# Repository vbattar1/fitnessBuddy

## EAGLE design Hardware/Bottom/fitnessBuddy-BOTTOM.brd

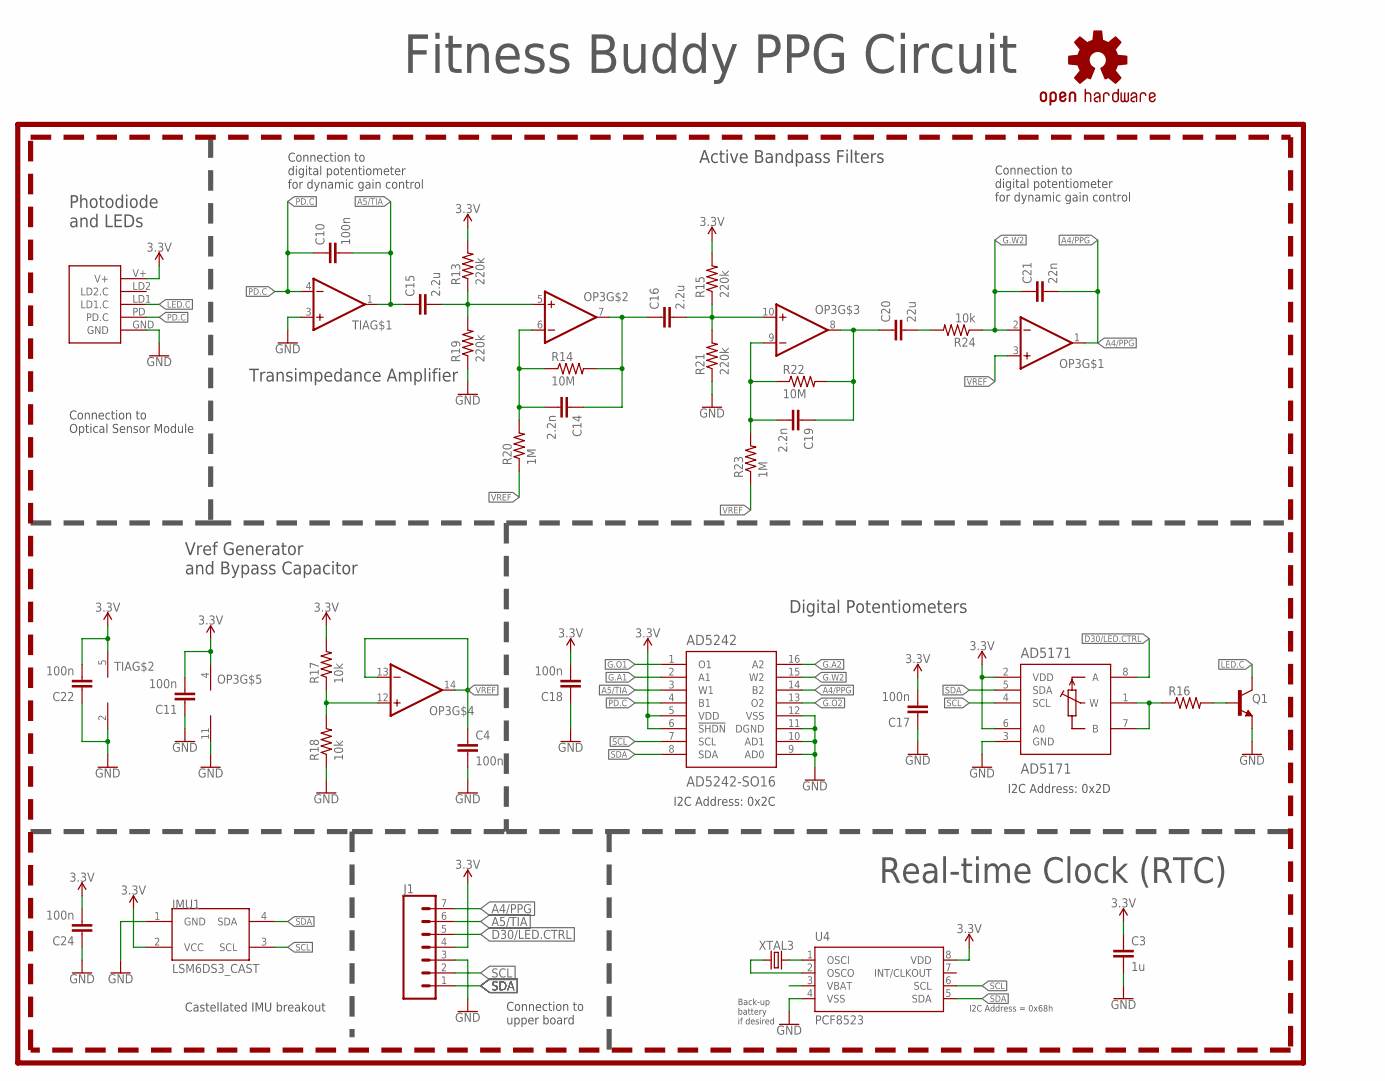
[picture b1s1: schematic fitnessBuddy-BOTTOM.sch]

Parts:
AD5171: AD5171; SOT-23-8
AD5242: AD5242-SO16; SO16
C3: 1u; C0603
C4, C10, C11, C17, C18, C22, C24: 100n; C0603
C14, C19: 2.2n; C0603
C15, C16: 2.2u; C0603
C20: 22u; C0603
C21: 22n; C0603
IMU1: LSM6DS3_CAST
J1: CONN_07-1.27MM; 1X07_1.27MM
LOGO1: REVISION.A; REV.A
LOGO2: OSHW-LOGOS; OSHW-LOGO-S
OP3: OP-QUAD-SO14; SO14
Q1: NPN-GENERIC; SOT23-3
R13, R15, R19, R21: 220k; R0603
R14, R22: 10M; R0603
R16: RESISTOR0603; R0603
R17, R18: 10k; R0402
R20, R23: 1M; R0603
R24: 10k; R0603
TIA: OP-SINGLEOT; SOT23-5
U4: PCF8523; SO8; DIGIKEY 568-5306-1-ND
U$3: PPG.MODULE.2
XTAL3: 32.7680kHz; 2-SMD.NOLEAD.2.0MMTO1.2MM

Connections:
3.3V: AD5171.2 (VDD), AD5171.6 (A0), AD5242.5 (VDD), AD5242.6 (!SHDN), C3.1, C11.2, C17.2, C18.2, C22.2, C24.2, IMU1.2 (VCC), J1.4, OP3.4 (V+), R13.2, R15.2, R17.2, TIA.5 (V+), U4.8 (VDD), U$3.V+
A4/PPG: AD5242.14 (B2), C21.2, J1.7, OP3.1 (OUT)
A5/TIA: AD5242.3 (W1), C10.2, C15.1, J1.6, TIA.1 (OUT)
D30/LED.CTRL: AD5171.8 (A), J1.5
G.A1: AD5242.2 (A1)
G.A2: AD5242.16 (A2)
G.O1: AD5242.1 (O1)
G.O2: AD5242.13 (O2)
G.W2: AD5242.15 (W2), C21.1, OP3.2 (-IN), R24.1
GND: AD5171.3 (GND), AD5242.9 (AD0), AD5242.10 (AD1), AD5242.11 (DGND), AD5242.12 (VSS), C3.2, C4.2, C11.1, C17.1, C18.1, C22.1, C24.1, IMU1.1 (GND), J1.3, OP3.11 (V-), Q1.2 (E), R18.1, R19.1, R21.1, TIA.2 (V-), TIA.3 (+IN), U4.4 (VSS), U$3.GND
LED.C: Q1.3 (C), U$3.LD1 (LD1.C)
unnamed: U4.2 (OSCO), XTAL3.P$1 (1)
unnamed: U4.1 (OSCI), XTAL3.P$2 (2)
unnamed: Q1.1 (B), R16.2
unnamed: AD5171.1 (W), AD5171.7 (B), R16.1
unnamed: OP3.12 (+IN), R17.1, R18.2
unnamed: C15.2, OP3.5 (+IN), R13.1, R19.2
unnamed: C14.2, OP3.6 (-IN), R14.1, R20.2
unnamed: C14.1, C16.1, OP3.7 (OUT), R14.2
unnamed: C16.2, OP3.10 (+IN), R15.1, R21.2
unnamed: C19.2, OP3.9 (-IN), R22.1, R23.2
unnamed: C19.1, C20.1, OP3.8 (OUT), R22.2
unnamed: C20.2, R24.2
PD.C: AD5242.4 (B1), C10.1, TIA.4 (-IN), U$3.PD (PD.C)
SCL: AD5171.4 (SCL), AD5242.7 (SCL), IMU1.3 (SCL), J1.2, U4.6 (SCL)
SDA: AD5171.5 (SDA), AD5242.8 (SDA), IMU1.4 (SDA), J1.1, U4.5 (SDA)
VBATT: U4.3 (VBAT)
VREF: C4.1, OP3.3 (+IN), OP3.13 (-IN), OP3.14 (OUT), R20.1, R23.1

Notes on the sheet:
Photodiode and LEDs
Active Bandpass Filters
Digital Potentiometers
Transimpedance Amplifier
I2C Address: 0x2C
I2C Address: 0x2D
I2C Address = 0x68h
Back-up battery if desired
Real-time Clock (RTC)
Connection to Optical Sensor Module
Connection to digital potentiometer for dynamic gain control
Connection to upper board
Castellated IMU breakout
Vref Generator and Bypass Capacitor
Fitness Buddy PPG Circuit

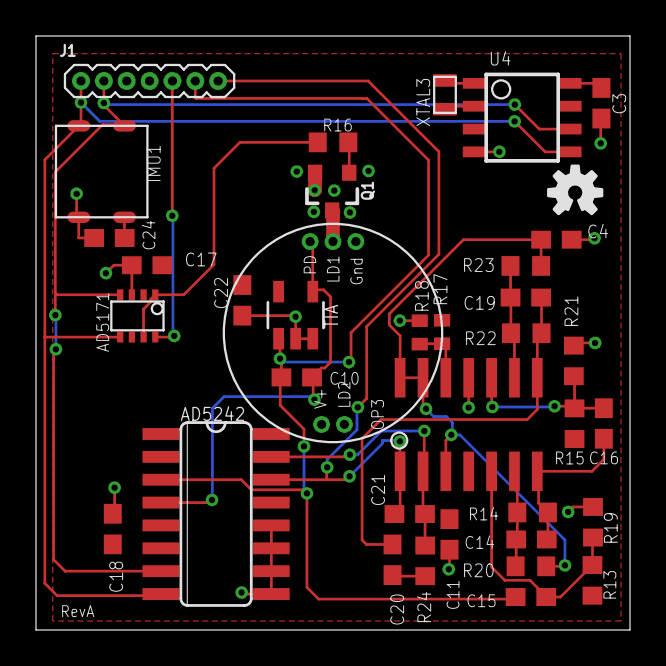
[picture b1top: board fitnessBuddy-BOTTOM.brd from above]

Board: 2 copper layers, 33.0 x 33.0 mm, 38 parts (0 on the bottom side), 23 nets.

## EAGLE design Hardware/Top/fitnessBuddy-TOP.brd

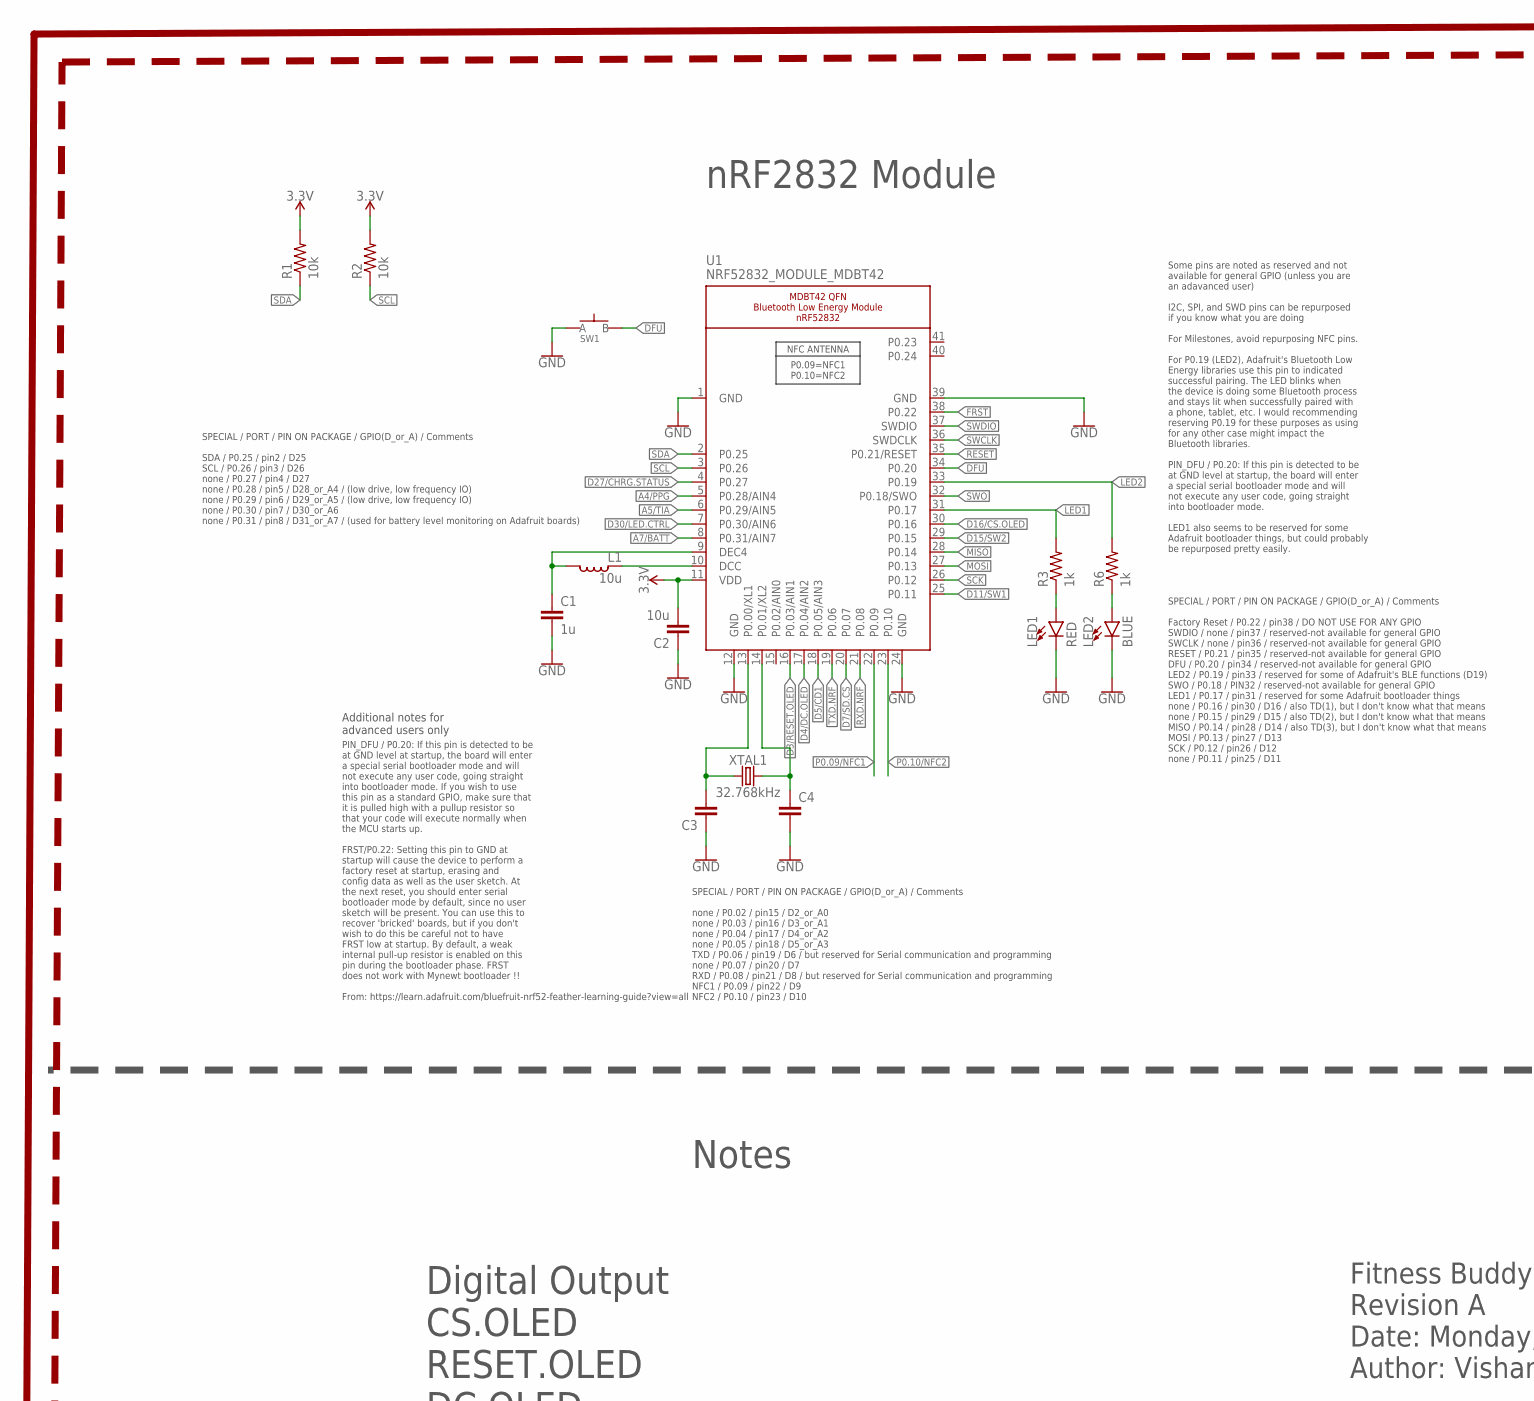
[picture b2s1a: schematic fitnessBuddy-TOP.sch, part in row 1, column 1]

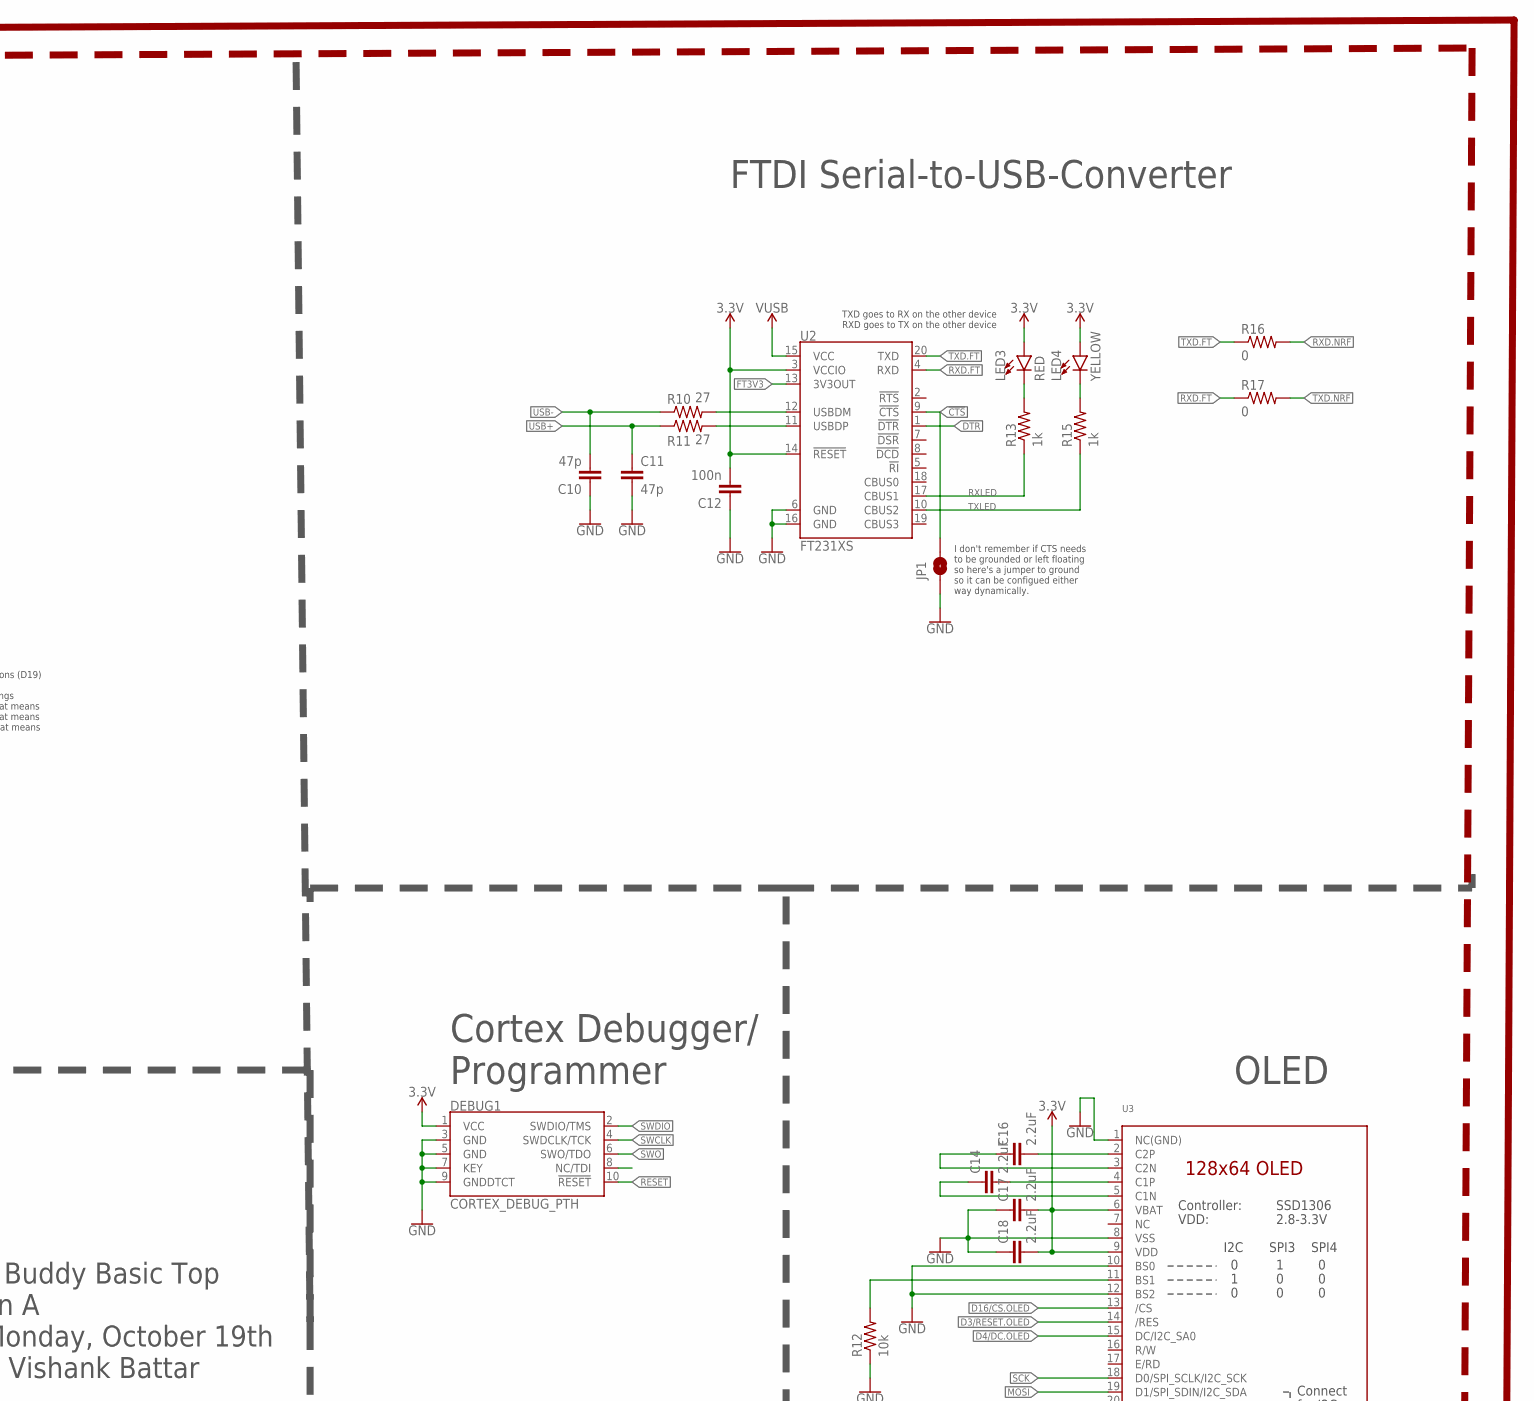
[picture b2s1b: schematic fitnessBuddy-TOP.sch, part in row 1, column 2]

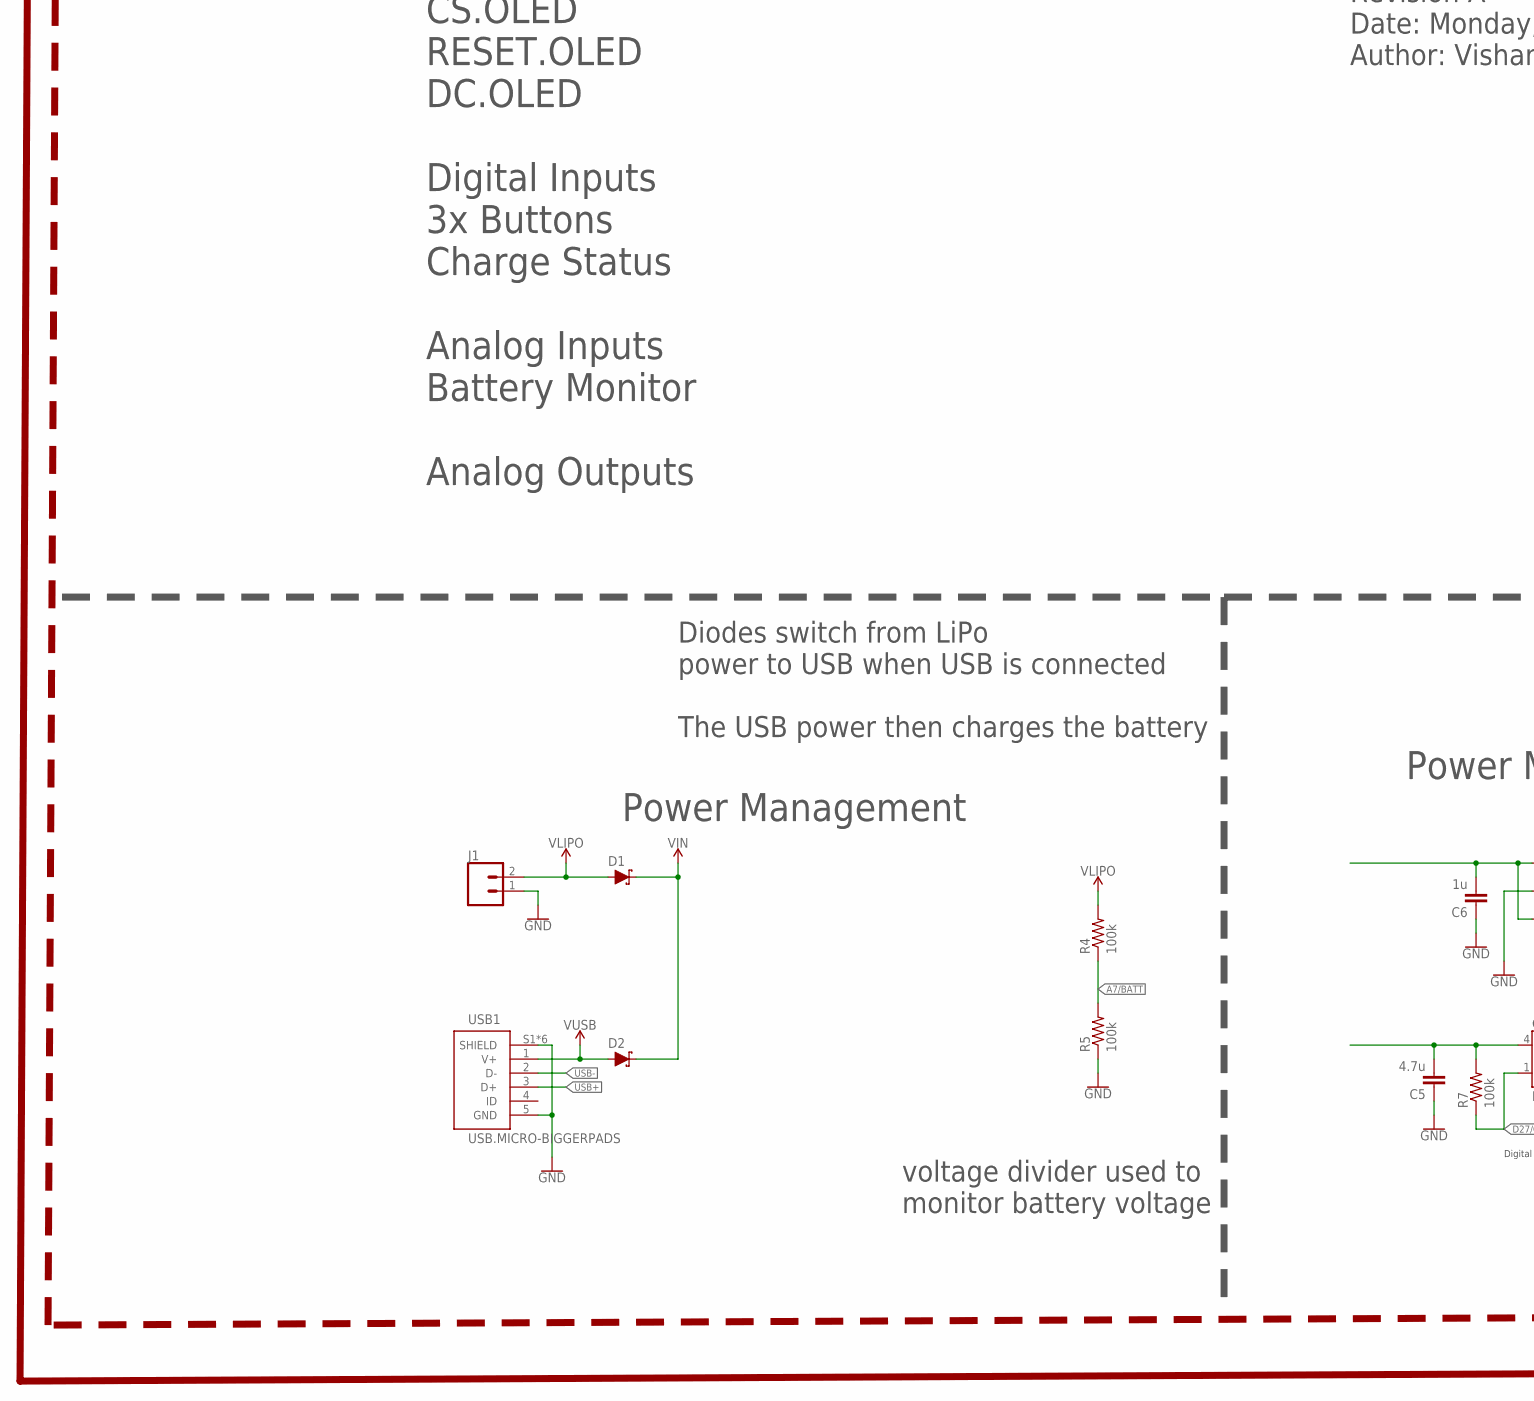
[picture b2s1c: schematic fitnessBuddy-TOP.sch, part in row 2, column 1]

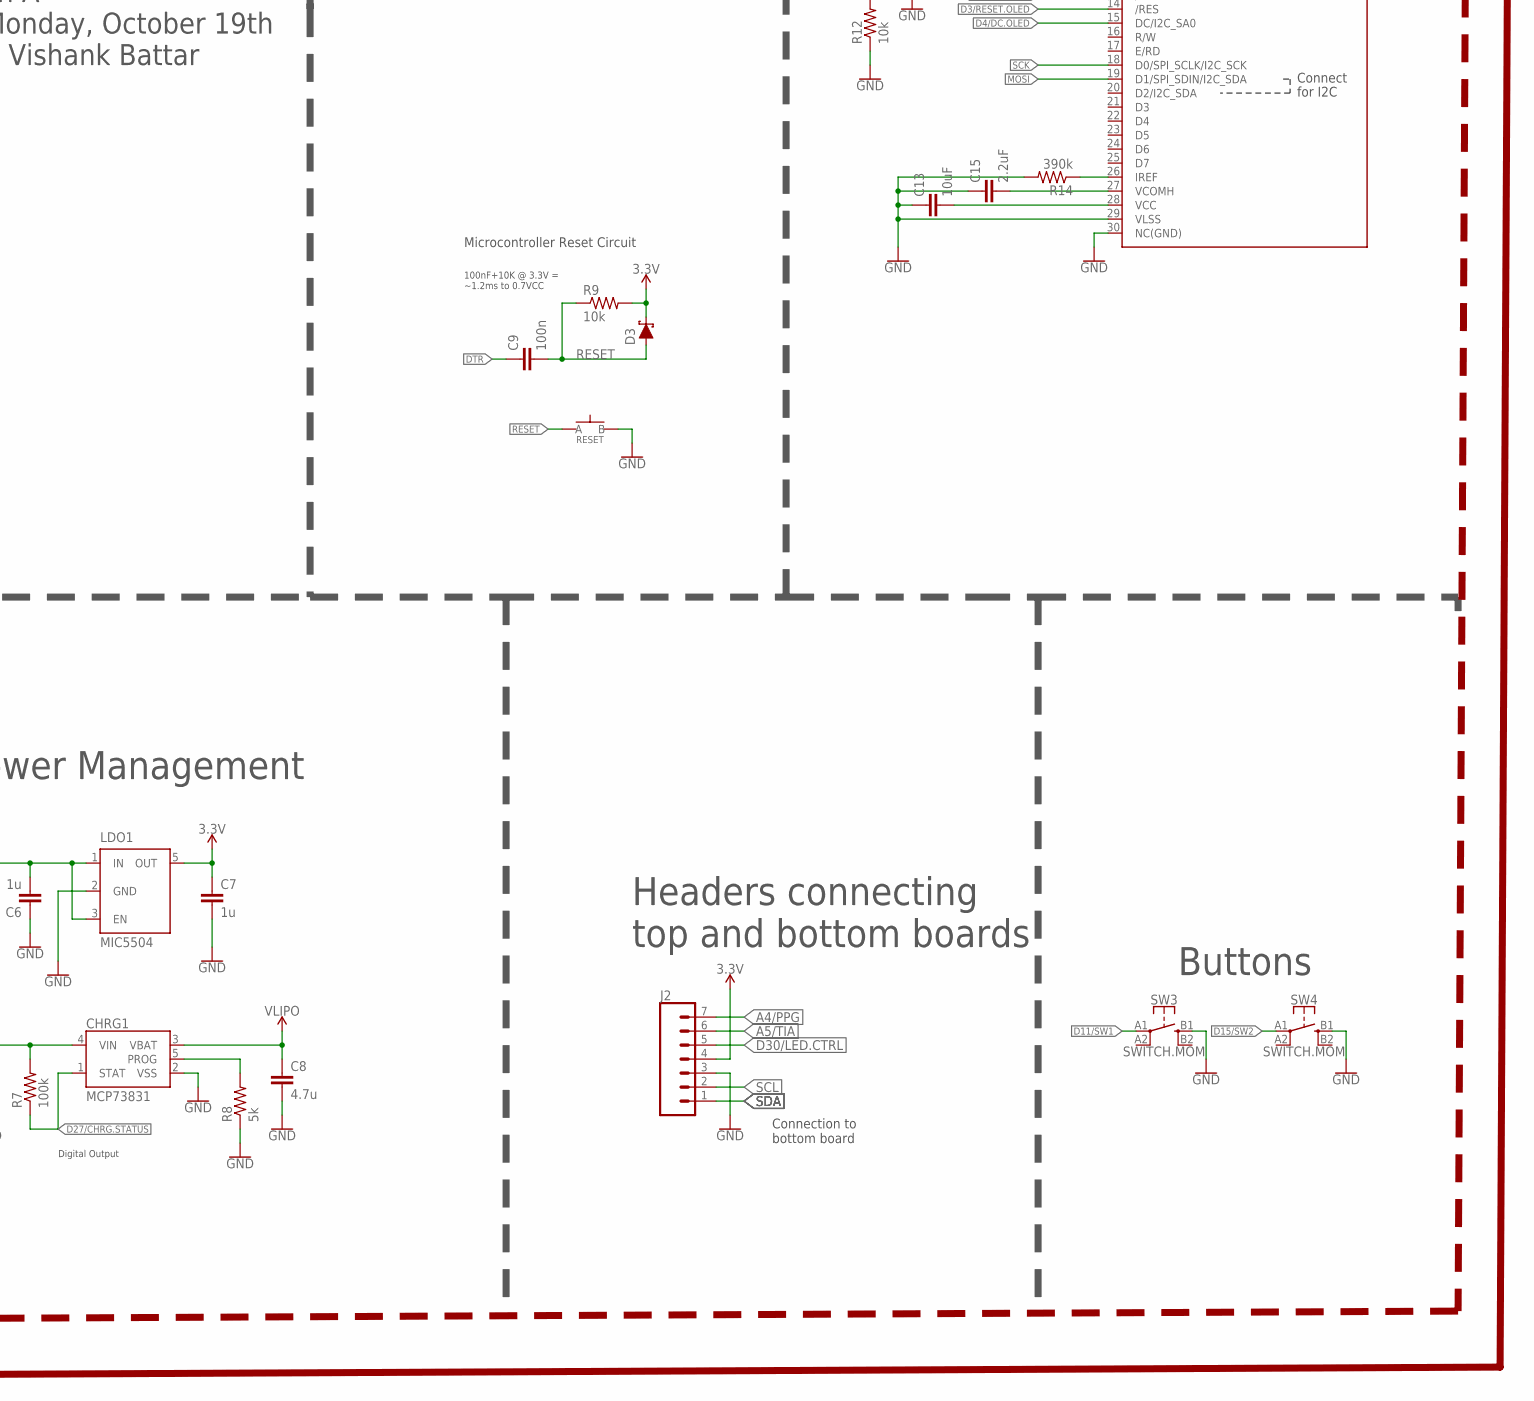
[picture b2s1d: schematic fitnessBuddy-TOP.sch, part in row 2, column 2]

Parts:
C1, C6, C7: 1u; C0603
C2: 10u; C0805
C3, C4: CAPACITOR0603; C0603
C5, C8: 4.7u; C0603
C9, C12: 100n; C0603
C10, C11: 47p; C0603
C13: 10uF; C0603
C14, C16, C17, C18: 2.2uF; C0402
C15: 2.2uF; C0603
CHRG1: MCP73831; SOT23-5
D1, D2, D3: SCHOTTKY-USC; USC
DEBUG1: CORTEX_DEBUG_PTH; 2X5-PTH-1.27MM
J1: CONN_02; 1X02
J2: CONN_07-1.27MM; 1X07_1.27MM
JP1: JUMPER-SMT_2_NO_SILK; SMT-JUMPER_2_NO_SILK
L1: 10u; L0603
LDO1: MIC5504; SOT23-5
LED1, LED3: RED; LED-0603
LED2: BLUE; LED-0603
LED4: YELLOW; LED-0603
R1, R2, R9, R12: 10k; R0603
R3, R6, R13, R15: 1k; R0603
R4, R5, R7: 100k; R0603
R8: 5k; R0603
R10, R11: 27; R0603
R14: 390k; R0603
R16, R17: 0; R0603
RESET: SPST-PTS830GG140-COPY.1-3; BUTTON-GULLWING
SW1: SPST-PTS830GG140-COPY.1-3; BUTTON-GULLWING
SW3, SW4: SWITCH.MOM; TACTILE_SWITCH_SMD_6.2MM_TALL
U1: NRF52832_MODULE_MDBT42; BLE_MODULE_RAYTAC_MDBT42
U2: FT231XS; SSOP20_L
U3: DISP_OLED_UG-2864HSWEG01-NO-WRAPAROUND; UG-2864HSWEG01_0.96IN_NO-WRAPAROUND
USB1: USB.MICRO-BIGGERPADS; USB-MICRO-01.BIGGERPADS
XTAL1: 32.768kHz; 2-SMD.NOLEAD.2.0MMTO1.2MM

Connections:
3.3V: C2.2, C7.1, C12.2, C17.2, C18.2, D3.- (C), DEBUG1.1 (VCC), J2.4, LDO1.5 (OUT), LED3.A, LED4.A, R1.2, R2.2, R9.2, U1.11 (VDD), U2.3 (VCCIO), U2.14 (!RESET), U3.6 (VBAT), U3.9 (VDD)
!CTS: JP1.2, U2.9 (!CTS)
A4/PPG: J2.7, U1.5 (P0.28/AIN4)
A5/TIA: J2.6, U1.6 (P0.29/AIN5)
A7/BATT: R4.1, R5.2, U1.8 (P0.31/AIN7)
D3/RESET.OLED: U1.16 (P0.03/AIN1), U3.14 (/RES)
D4/DC.OLED: U1.17 (P0.04/AIN2), U3.15 (DC/I2C_SA0)
D5/CD1: U1.18 (P0.05/AIN3)
D7/SD.CS: U1.20 (P0.07)
D11/SW1: SW3.A1 (1), U1.25 (P0.11)
D15/SW2: SW4.A1 (1), U1.29 (P0.15)
D16/CS.OLED: U1.30 (P0.16), U3.13 (/CS)
D27/CHRG.STATUS: CHRG1.1 (STAT), R7.1, U1.4 (P0.27)
D30/LED.CTRL: J2.5, U1.7 (P0.30/AIN6)
DFU: SW1.3 (B), U1.34 (P0.20)
DTR: C9.1, U2.1 (!DTR)
FRST: U1.38 (P0.22)
FT3V3: U2.13 (3V3OUT)
GND: C1.2, C2.1, C3.1, C4.2, C5.1, C6.1, C7.2, C8.2, C10.1, C11.2, C12.1, C13.1, C15.1, C17.1, C18.1, CHRG1.2 (VSS), DEBUG1.3 (GND), DEBUG1.5 (GND), DEBUG1.7 (KEY), DEBUG1.9 (GNDDTCT), J1.1, J2.3, JP1.1, LDO1.2 (GND), LED1.C, LED2.C, R5.1, R8.1, R12.1, R14.2, RESET.3 (B), SW1.1 (A), SW3.B1 (3), SW4.B1 (3), U1.1 (GND), U1.12 (GND), U1.24 (GND), U1.39 (GND), U2.6 (GND), U2.16 (GND), U3.1 (NC(GND)), U3.8 (VSS), U3.10 (BS0), U3.12 (BS2), U3.29 (VLSS), U3.30 (NC(GND)), USB1.5 (GND), USB1.S1 (SHIELD), USB1.S2 (SHIELD), USB1.S3 (SHIELD), USB1.S4 (SHIELD), USB1.S5 (SHIELD), USB1.S6 (SHIELD)
LED1: R3.2, U1.31 (P0.17)
LED2: R6.2, U1.33 (P0.19)
MISO: U1.28 (P0.14)
MOSI: U1.27 (P0.13), U3.19 (D1/SPI_SDIN/I2C_SDA)
unnamed: R12.2, U3.11 (BS1)
unnamed: R14.1, U3.26 (IREF)
unnamed: C16.2, U3.2 (C2P)
unnamed: C3.2, U1.13 (P0.00/XL1), XTAL1.P$1 (1)
unnamed: C16.1, U3.3 (C2N)
unnamed: C4.1, U1.14 (P0.01/XL2), XTAL1.P$2 (2)
unnamed: C14.2, U3.4 (C1P)
unnamed: C14.1, U3.5 (C1N)
unnamed: LED1.A, R3.1
unnamed: LED2.A, R6.1
unnamed: L1.1, U1.10 (DCC)
unnamed: C1.1, L1.2, U1.9 (DEC4)
unnamed: C13.2, U3.28 (VCC)
unnamed: C15.2, U3.27 (VCOMH)
unnamed: CHRG1.5 (PROG), R8.2
unnamed: C5.2, CHRG1.4 (VIN), R7.2
unnamed: R10.2, U2.12 (USBDM)
unnamed: R11.2, U2.11 (USBDP)
unnamed: LED3.C, R13.2
unnamed: LED4.C, R15.2
P0.09/NFC1: U1.22 (P0.09)
P0.10/NFC2: U1.23 (P0.10)
RESET: C9.2, D3.+ (A), DEBUG1.10 (!RESET), R9.1, RESET.1 (A), U1.35 (P0.21/RESET)
RXD.FT: R17.1, U2.4 (RXD)
RXD.NRF: R16.2, U1.21 (P0.08)
RXLED: R13.1, U2.17 (CBUS1)
SCK: U1.26 (P0.12), U3.18 (D0/SPI_SCLK/I2C_SCK)
SCL: J2.2, R2.1, U1.3 (P0.26)
SDA: J2.1, R1.1, U1.2 (P0.25)
SWCLK: DEBUG1.4 (SWDCLK/TCK), U1.36 (SWDCLK)
SWDIO: DEBUG1.2 (SWDIO/TMS), U1.37 (SWDIO)
SWO: DEBUG1.6 (SWO/TDO), U1.32 (P0.18/SWO)
TXD.FT: R16.1, U2.20 (TXD)
TXD.NRF: R17.2, U1.19 (P0.06)
TXLED: R15.1, U2.10 (CBUS2)
USB+: C11.1, R11.1, USB1.3 (D+)
USB-: C10.2, R10.1, USB1.2 (D-)
VIN: C6.2, D1.- (C), D2.- (C), LDO1.1 (IN), LDO1.3 (EN)
VLIPO: C8.1, CHRG1.3 (VBAT), D1.+ (A), J1.2, R4.2
V_USB: D2.+ (A), U2.15 (VCC), USB1.1 (V+)

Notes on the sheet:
Microcontroller Reset Circuit
100nF+10K @ 3.3V = ~1.2ms to 0.7VCC
SPECIAL / PORT / PIN ON PACKAGE / GPIO(D_or_A) / Comments SDA / P0.25 / pin2 / D25 SCL / P0.26 / pin3 / D26 none / P0.27 / pin4 / D27 none / P0.28 / pin5 / D28_or_A4 / (low drive, low frequency IO) none / P0.29 / pin6 / D29_or_A5 / (low drive, low frequency IO) none / P0.30 / pin7 / D30_or_A6 none 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
SPECIAL / PORT / PIN ON PACKAGE / GPIO(D_or_A) / Comments none / P0.02 / pin15 / D2_or_A0 none / P0.03 / pin16 / D3_or_A1 none / P0.04 / pin17 / D4_or_A2 none / P0.05 / pin18 / D5_or_A3 TXD / P0.06 / pin19 / D6 / but reserved for Serial communication and programming none / P0.07 / pin20 / D7 RXD / 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
SPECIAL / PORT / PIN ON PACKAGE / GPIO(D_or_A) / Comments Factory Reset / P0.22 / pin38 / DO NOT USE FOR ANY GPIO SWDIO / none / pin37 / reserved-not available for general GPIO SWCLK / none / pin36 / reserved-not available for general GPIO RESET / P0.21 / pin35 / reserved-not available for general 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
Some pins are noted as reserved and not available for general GPIO (unless you are an adavanced user) I2C, SPI, and SWD pins can be repurposed if you know what you are doing For Milestones, avoid repurposing NFC pins. For P0.19 (LED2), Adafruit's Bluetooth Low Energy libraries use this pin to indic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
PIN_DFU / P0.20: If this pin is detected to be at GND level at startup, the board will enter a special serial bootloader mode and will not execute any user code, going straight into bootloader mode. If you wish to use this pin as a standard GPIO, make sure that it is pulled high with a pullup resis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
Additional notes for advanced users only
nRF2832 Module
OLED
Power Management
Buttons
Cortex Debugger/ Programmer
Digital Output CS.OLED RESET.OLED DC.OLED Digital Inputs 3x Buttons Charge Status Analog Inputs Battery Monitor Analog Outputs
TXD goes to RX on the other device RXD goes to TX on the other device
I don't remember if CTS needs to be grounded or left floating so here's a jumper to ground so it can be configued either way dynamically.
FTDI Serial-to-USB-Converter
Notes
Connection to bottom board
Digital Output
Fitness Buddy Basic Top Revision A Date: Monday, October 19th Author: Vishank Battar
Diodes switch from LiPo power to USB when USB is connected The USB power then charges the battery
voltage divider used to monitor battery voltage
Headers connecting top and bottom boards

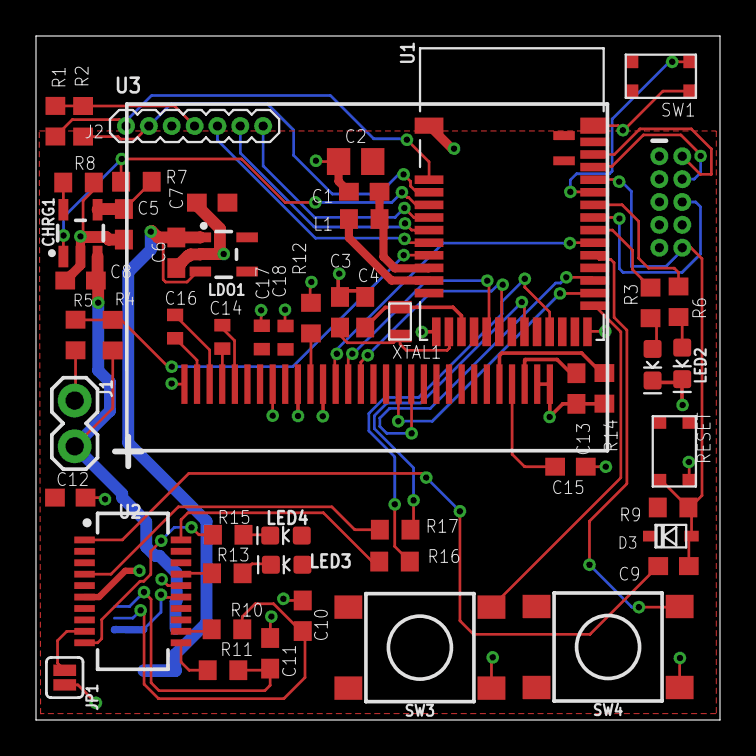
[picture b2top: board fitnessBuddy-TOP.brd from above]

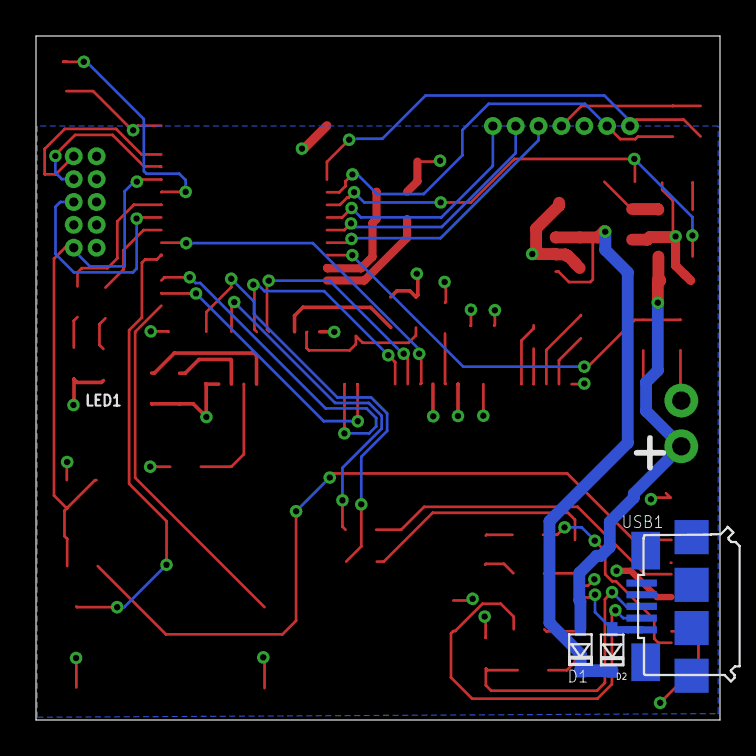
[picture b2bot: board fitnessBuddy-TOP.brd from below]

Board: 2 copper layers, 38.0 x 38.0 mm, 58 parts (3 on the bottom side), 56 nets.

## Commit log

2020-06-02 added to repo
2020-06-04 changed name to name of smartwatch
2020-06-04 created new file structure for repository
2020-06-04 changed name of .gitignore file
2020-06-04 deleted improperly named gitignore file
2020-06-04 created files properly through respective programs
2020-06-06 imported and organized design blocks on top and bottom boards
2020-06-06 completed adding design blocks to top and bottom boards
2020-06-11 added FTDI controller
2020-06-18 finished bottom board and schematic
2020-06-18 started to route bottom board
2020-06-25 Made progress on routing bottom board
2020-06-25 finished routing PPG Board
2020-07-03 Began routing top board
2020-07-04 routed top board
2020-07-17 Reorganized top and bottom boards, went back and rerouted some of top board (basically did take 005 and take 006)
2020-07-17 finished routing power management on top board
2020-07-24 finished halfway through take 007. organized board/ connected airwires
2020-10-19 organized top board
2020-10-19 got rid of isolated polygons
2020-10-20 reorganized bottom boards, added RTC to bottom board, and added notes to top schematic
2020-10-28 fixed pinout connecting bottom and top boards also added ppg module files
